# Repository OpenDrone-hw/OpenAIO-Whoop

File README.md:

# OpenAIO-Whoop

An all-in-one board for 1S: 65 and 75 mm tiny whoops, 1S toothpicks and 1S
long range on an 18650. Flight controller,
four brushless ESC channels, an ExpressLRS receiver and an onboard analog VTX
on the 25.5 x 25.5 mm whoop mounting pattern. The 1S sibling of
[OpenAIO](https://github.com/OpenDrone-hw/OpenAIO), which covers 3S to 6S on
the same mounting pattern.

## Why

Whoops are where an AIO is not a convenience but the only option: there is no room for a stack and no weight budget for connectors. 2S and up is OpenAIO's range, so what is left for a second board is 1S, where the power tree starts from a single cell and everything above battery voltage has to be boosted.

Analog is the reason this board is separate rather than a variant. A 1S whoop is the last class still flying analog in volume, and an onboard VTX is what makes the board worth building instead of pointing people at a digital AIO with an HD port.

## Specifications

| | |
|---|---|
| Target class | 1S whoops, 65 to 85 mm |
| Mounting | 25.5 x 25.5 mm, three D3.55 ear holes |
| Board | 26.4 mm body, 8-layer HDI 1+6+1, 0.997 mm |
| Input | 1S LiPo, solder pads J2 (+) and J3 (-) |
| MCU | RP2354A, 2 MB in-package flash |
| IMU | BMI270 on SPI |
| Blackbox | 16 MB SPI NOR flash (PY25Q128HA) |
| ESC | 4 channels, EFM8BB51 + 3 AGM210MAP half-bridges each, bidirectional DShot, Bluejay |
| Current sense | 0.5 mohm shunt + INA186A3, 50 mV/A |
| Receiver | Onboard ExpressLRS 2.4 GHz, ESP32-PICO-V3 + SX1281, wire antenna |
| Video | Onboard analog VTX, RTC6705 + SE5004L PA, U.FL |
| OSD | Analog, PIO framebuffer |
| Digital video | DJI O4 Lite pads: J26 VHD (+5V_BST), J28 TX0, J29 RX0, J27 GND (UART0); JST SH 1.0 mm 4-pin plug J35 (1 VHD, 2 GND, 3 TX, 4 RX) |
| Motors | Molex PicoBlade 1.25 mm 3-pin lands, plug or solder |
| USB | JST SH 1.0 mm 4-pin, J31 |
| Camera | JST SUR 0.8 mm 3-pin plug J32, solder pads J23 and J24 |
| Firmware | Betaflight (target in this repo), Bluejay, ExpressLRS |

Technical write-up, part list and layout constraints: [AGENTS.md](AGENTS.md). Pin map: [research/PINMAP.md](research/PINMAP.md). Firmware: [Betaflight target](firmware/betaflight/README.md), [ExpressLRS binding](firmware/expresslrs/README.md).

Open `hardware/OpenAIO-Whoop.kicad_pro` in KiCad 10 and keep the hardware folder together. The images above are renders of the routed board; this is not a manufacturing release.

## Constraints

- 25.5 x 25.5 mm mounting pattern, shared with OpenAIO.
- 1S only. 2S and above is OpenAIO.
- Motor plugs, USB, battery pads and camera plug follow the BetaFPV Matrix 1S 5IN1 II positions, so leads and cables reach as on that board.
- FC section follows the [OpenFC Lite 20x20](https://github.com/OpenDrone-hw/OpenFC-Lite-Mini) RP2354A design; receiver follows [OpenRX-Lite-UFL](https://github.com/OpenDrone-hw/OpenRX-Lite-UFL) (SX1281) on an ESP32-PICO-V3 that talks CRSF to the FC and also controls the VTX.
- Passives 0201 and up.
- No battery protection on the board: no reverse-polarity protection, no TVS, no low-cell cutoff.

### VTX control path

| Item | Value |
|---|---|
| Protocol | ExpressLRS MSP-VTX, CRSF receiver on UART1 (GPIO8/9) |
| VTX owner | ESP32-PICO-V3 drives the RTC6705 over SPI and the SE5004L reference through PA_EN (ESP32 GPIO21) |
| Pit mode | Does not drop PA_EN and does not stop SPI activity (see firmware/expresslrs/README.md) |
| HD hold-off | RP2354A GPIO19 (`HD_EN`) high permits analog VTX power, low switches it off; fixed HD builds set `pinio_config = 1,1,1,1` |

## Prior art

- [OpenFC Lite 20x20](https://github.com/OpenDrone-hw/OpenFC-Lite-Mini) and [OpenRX-Lite-UFL](https://github.com/OpenDrone-hw/OpenRX-Lite-UFL): the FC and RX stages this board follows.
- [OpenAIO](https://github.com/OpenDrone-hw/OpenAIO): the 3S to 6S board on the same mounting pattern.
- [OpenVTX](https://github.com/OpenDrone-hw/OpenVTX): the line's RTC6705 analog VTX.
- BetaFPV Matrix 1S 5IN1 II: the class reference.

## In the line

What pairs with what, and what is available:
[opendrone.be](https://opendrone.be).

## Contributing

See [CONTRIBUTING.md](CONTRIBUTING.md). KiCad files cannot be merged, so say what you intend to change before you do, on [Discord](https://discord.gg/v3sWmTcx3R).

Clone with the shared library:

```sh
git clone --recursive https://github.com/OpenDrone-hw/OpenAIO-Whoop
git submodule update --init      # after a plain git clone
```

Catalogue 3D models resolve through the project text variable `OPENDRONE_LIB` (`${KIPRJMOD}/KiCad-Library`), so without the submodule the 3D view shows bare pads.

A repository holds design files only. Sourcing (suppliers, prices, quotes, RFQs, contacts) is handled by Incutec and never lives in OpenDrone repositories.

## License

Hardware licensed under [CERN-OHL-S-2.0](https://ohwr.org/cern_ohl_s_v2.txt),
see [LICENSE](LICENSE).

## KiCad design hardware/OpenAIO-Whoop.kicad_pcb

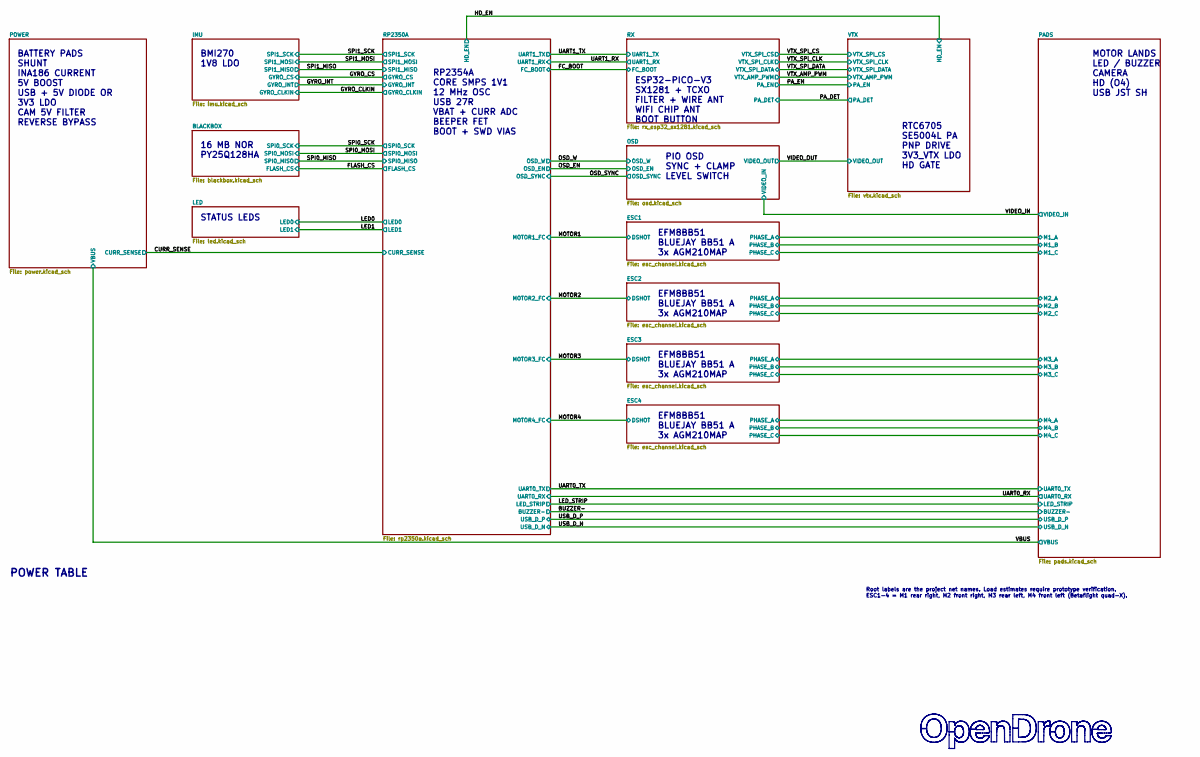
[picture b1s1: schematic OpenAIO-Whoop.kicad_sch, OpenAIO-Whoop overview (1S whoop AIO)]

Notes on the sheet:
PIO OSD SYNC + CLAMP LEVEL SWITCH
EFM8BB51 BLUEJAY BB51 A 3x AGM210MAP
16 MB NOR PY25Q128HA
POWER TABLE
STATUS LEDS
ESP32-PICO-V3 SX1281 + TCXO FILTER + WIRE ANT WIFI CHIP ANT BOOT BUTTON
BATTERY PADS SHUNT INA186 CURRENT 5V BOOST USB + 5V DIODE OR 3V3 LDO CAM 5V FILTER REVERSE BYPASS
MOTOR LANDS LED / BUZZER CAMERA HD (O4) USB JST SH
RTC6705 SE5004L PA PNP DRIVE 3V3_VTX LDO HD GATE
RP2354A CORE SMPS 1V1 12 MHz OSC USB 27R VBAT + CURR ADC BEEPER FET BOOT + SWD VIAS
BMI270 1V8 LDO
Root labels are the project net names. Load estimates require prototype verification. ESC1-4 = M1 rear right, M2 front right, M3 rear left, M4 front left (Betaflight quad-X).

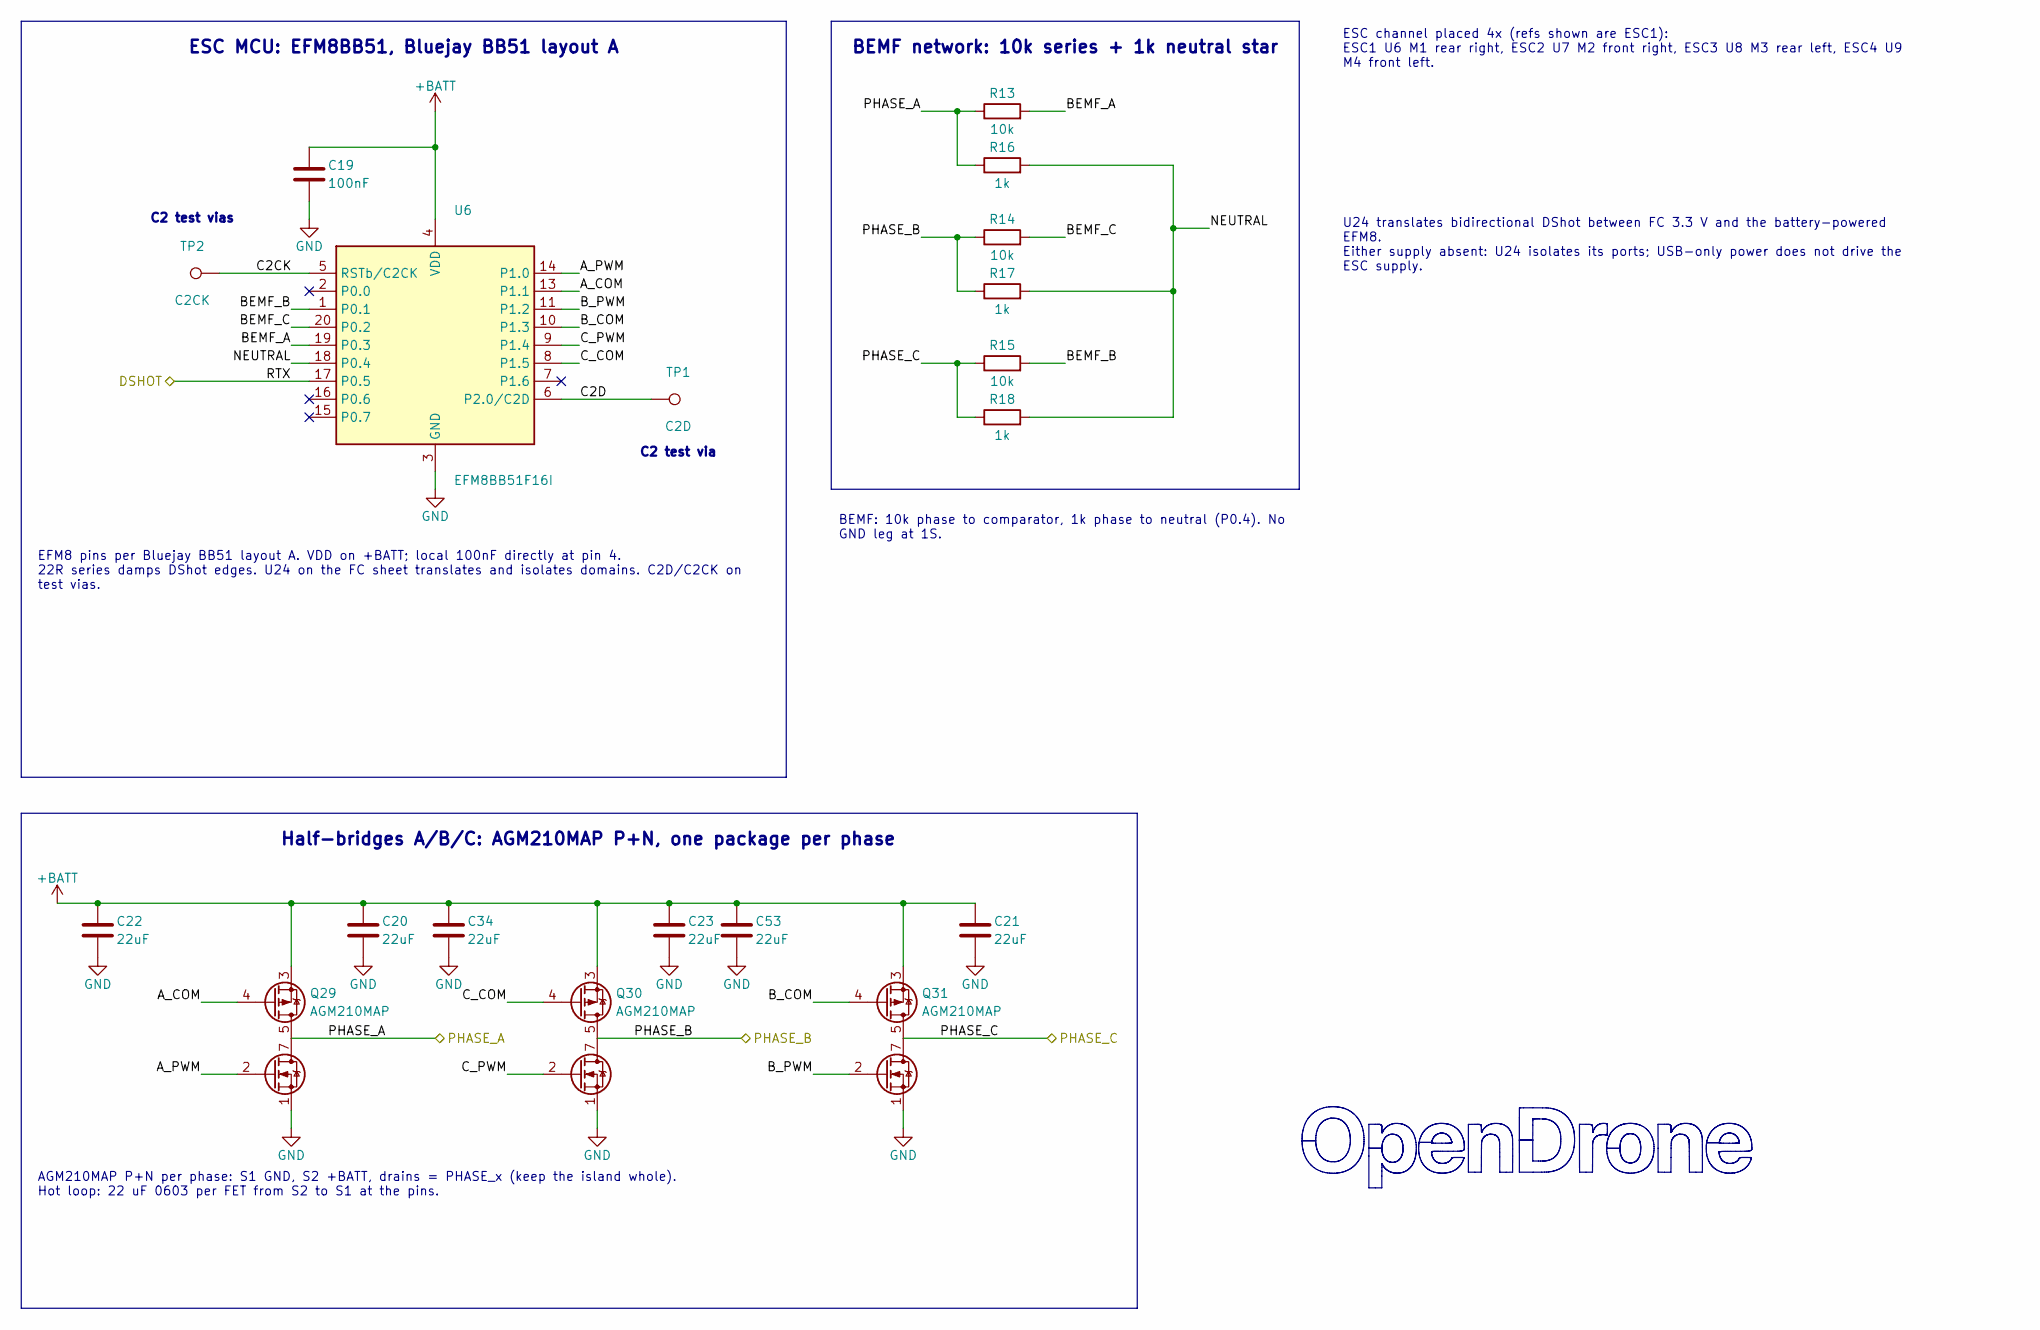
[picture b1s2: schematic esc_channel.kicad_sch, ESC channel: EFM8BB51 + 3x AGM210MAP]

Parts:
C19: 100nF; C_0201_0603Metric_L; MPN GRM033C81E104KE14D; LCSC C181047
C20, C21, C22, C23, C34, C53: 22uF; C_0603_1608Metric_L; MPN GRM188C80J226ME15D; LCSC C393031
Q29, Q30, Q31: AGM210MAP; AGM_PDFN-8-2EP_3.3x3.3mm_AGM210MAP_L; MPN AGM210MAP; LCSC C7431169
R13, R14, R15: 10k; R_0201_0603Metric_L; MPN RC0201FR-0710KL; LCSC C106225
R16, R17, R18: 1k; R_0201_0603Metric_L; MPN RC0201FR-071KL; LCSC C138165
TP1: C2D; TestPoint_Pad_D0.8mm
TP2: C2CK; TestPoint_Pad_D0.8mm
U6: EFM8BB51F16I; QFN-20_3x3mm_P0.5mm_EFM8BB51_L; MPN EFM8BB51F16I-C-QFN20R; LCSC C3232998

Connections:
+BATT: C19.1, C20.1, C21.1, C22.1, C23.1, C34.1, Q29.3 (S2), Q30.3 (S2), Q31.3 (S2), U6.4 (VDD); also elsewhere on the board
/ESC1/A_COM: Q29.4 (G2), U6.13 (P1.1)
/ESC1/A_PWM: Q29.2 (G1), U6.14 (P1.0)
/ESC1/BEMF_A: R13.2, U6.19 (P0.3)
/ESC1/BEMF_B: R15.2, U6.1 (P0.1)
/ESC1/BEMF_C: R14.2, U6.20 (P0.2)
/ESC1/B_COM: Q31.4 (G2), U6.10 (P1.3)
/ESC1/B_PWM: Q31.2 (G1), U6.11 (P1.2)
/ESC1/C2CK: TP2.1 (1_1), U6.5 (RSTb/C2CK)
/ESC1/C2D: TP1.1 (1_1), U6.6 (P2.0/C2D)
/ESC1/C_COM: Q30.4 (G2), U6.8 (P1.5)
/ESC1/C_PWM: Q30.2 (G1), U6.9 (P1.4)
/ESC1/NEUTRAL: R16.2, R17.2, R18.2, U6.18 (P0.4)
/ESC1/PHASE_A: Q29.5 (D2), Q29.6 (D2), Q29.7 (D1), Q29.8 (D1), R13.1, R16.1; also elsewhere on the board
/ESC1/PHASE_B: Q30.5 (D2), Q30.6 (D2), Q30.7 (D1), Q30.8 (D1), R14.1, R17.1; also elsewhere on the board
/ESC1/PHASE_C: Q31.5 (D2), Q31.6 (D2), Q31.7 (D1), Q31.8 (D1), R15.1, R18.1; also elsewhere on the board
/MOTOR1: U6.17 (P0.5); also elsewhere on the board
GND: C19.2, C20.2, C21.2, C22.2, C23.2, C34.2, Q29.1 (S1), Q30.1 (S1), Q31.1 (S1), U6.3 (GND), U6.12 (GND), U6.21 (GND); also elsewhere on the board

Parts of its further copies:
C24, C26, C27, C28, C29, C30, C32, C33, C35, C36, C38, C39, C40, C41, C43, C63: 22uF; C_0603_1608Metric_L; MPN GRM188C80J226ME15D; LCSC C393031
Q32, Q33, Q34, Q35, Q36, Q37, Q38, Q39, Q40: AGM210MAP; AGM_PDFN-8-2EP_3.3x3.3mm_AGM210MAP_L; MPN AGM210MAP; LCSC C7431169
R20, R21, R22, R27, R28, R29, R34, R35, R36: 10k; R_0201_0603Metric_L; MPN RC0201FR-0710KL; LCSC C106225
R23, R24, R25, R30, R31, R32, R37, R38, R39: 1k; R_0201_0603Metric_L; MPN RC0201FR-071KL; LCSC C138165
TP3, TP5, TP7: C2D; TestPoint_Pad_D0.8mm
TP4, TP6, TP8: C2CK; TestPoint_Pad_D0.8mm
U7, U8, U9: EFM8BB51F16I; QFN-20_3x3mm_P0.5mm_EFM8BB51_L; MPN EFM8BB51F16I-C-QFN20R; LCSC C3232998

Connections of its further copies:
+BATT: C24.1, C26.1, C27.1, C28.1, C29.1, C30.1, C32.1, C33.1, C35.1, C36.1, C38.1, C39.1, C40.1, C41.1, C43.1, C63.1, Q32.3 (S2), Q33.3 (S2), Q34.3 (S2), Q35.3 (S2), Q36.3 (S2), Q37.3 (S2), Q38.3 (S2), Q39.3 (S2), Q40.3 (S2), U7.4 (VDD), U8.4 (VDD), U9.4 (VDD); also elsewhere on the board
/ESC2/A_COM: Q32.4 (G2), U7.13 (P1.1)
/ESC2/A_PWM: Q32.2 (G1), U7.14 (P1.0)
/ESC2/BEMF_A: R20.2, U7.19 (P0.3)
/ESC2/BEMF_B: R22.2, U7.1 (P0.1)
/ESC2/BEMF_C: R21.2, U7.20 (P0.2)
/ESC2/B_COM: Q34.4 (G2), U7.10 (P1.3)
/ESC2/B_PWM: Q34.2 (G1), U7.11 (P1.2)
/ESC2/C2CK: TP4.1 (1_1), U7.5 (RSTb/C2CK)
/ESC2/C2D: TP3.1 (1_1), U7.6 (P2.0/C2D)
/ESC2/C_COM: Q33.4 (G2), U7.8 (P1.5)
/ESC2/C_PWM: Q33.2 (G1), U7.9 (P1.4)
/ESC2/NEUTRAL: R23.2, R24.2, R25.2, U7.18 (P0.4)
/ESC2/PHASE_A: Q32.5 (D2), Q32.6 (D2), Q32.7 (D1), Q32.8 (D1), R20.1, R23.1; also elsewhere on the board
/ESC2/PHASE_B: Q33.5 (D2), Q33.6 (D2), Q33.7 (D1), Q33.8 (D1), R21.1, R24.1; also elsewhere on the board
/ESC2/PHASE_C: Q34.5 (D2), Q34.6 (D2), Q34.7 (D1), Q34.8 (D1), R22.1, R25.1; also elsewhere on the board
/ESC3/A_COM: Q35.4 (G2), U8.13 (P1.1)
/ESC3/A_PWM: Q35.2 (G1), U8.14 (P1.0)
/ESC3/BEMF_A: R27.2, U8.19 (P0.3)
/ESC3/BEMF_B: R29.2, U8.1 (P0.1)
/ESC3/BEMF_C: R28.2, U8.20 (P0.2)
/ESC3/B_COM: Q37.4 (G2), U8.10 (P1.3)
/ESC3/B_PWM: Q37.2 (G1), U8.11 (P1.2)
/ESC3/C2CK: TP6.1 (1_1), U8.5 (RSTb/C2CK)
/ESC3/C2D: TP5.1 (1_1), U8.6 (P2.0/C2D)
/ESC3/C_COM: Q36.4 (G2), U8.8 (P1.5)
/ESC3/C_PWM: Q36.2 (G1), U8.9 (P1.4)
/ESC3/NEUTRAL: R30.2, R31.2, R32.2, U8.18 (P0.4)
/ESC3/PHASE_A: Q35.5 (D2), Q35.6 (D2), Q35.7 (D1), Q35.8 (D1), R27.1, R30.1; also elsewhere on the board
/ESC3/PHASE_B: Q36.5 (D2), Q36.6 (D2), Q36.7 (D1), Q36.8 (D1), R28.1, R31.1; also elsewhere on the board
/ESC3/PHASE_C: Q37.5 (D2), Q37.6 (D2), Q37.7 (D1), Q37.8 (D1), R29.1, R32.1; also elsewhere on the board
/ESC4/A_COM: Q38.4 (G2), U9.13 (P1.1)
/ESC4/A_PWM: Q38.2 (G1), U9.14 (P1.0)
/ESC4/BEMF_A: R34.2, U9.19 (P0.3)
/ESC4/BEMF_B: R36.2, U9.1 (P0.1)
/ESC4/BEMF_C: R35.2, U9.20 (P0.2)
/ESC4/B_COM: Q40.4 (G2), U9.10 (P1.3)
/ESC4/B_PWM: Q40.2 (G1), U9.11 (P1.2)
/ESC4/C2CK: TP8.1 (1_1), U9.5 (RSTb/C2CK)
/ESC4/C2D: TP7.1 (1_1), U9.6 (P2.0/C2D)
/ESC4/C_COM: Q39.4 (G2), U9.8 (P1.5)
/ESC4/C_PWM: Q39.2 (G1), U9.9 (P1.4)
/ESC4/NEUTRAL: R37.2, R38.2, R39.2, U9.18 (P0.4)
/ESC4/PHASE_A: Q38.5 (D2), Q38.6 (D2), Q38.7 (D1), Q38.8 (D1), R34.1, R37.1; also elsewhere on the board
/ESC4/PHASE_B: Q39.5 (D2), Q39.6 (D2), Q39.7 (D1), Q39.8 (D1), R35.1, R38.1; also elsewhere on the board
/ESC4/PHASE_C: Q40.5 (D2), Q40.6 (D2), Q40.7 (D1), Q40.8 (D1), R36.1, R39.1; also elsewhere on the board
/MOTOR2: U7.17 (P0.5); also elsewhere on the board
/MOTOR3: U8.17 (P0.5); also elsewhere on the board
/MOTOR4: U9.17 (P0.5); also elsewhere on the board
GND: C24.2, C26.2, C27.2, C28.2, C29.2, C30.2, C32.2, C33.2, C35.2, C36.2, C38.2, C39.2, C40.2, C41.2, C43.2, C63.2, Q32.1 (S1), Q33.1 (S1), Q34.1 (S1), Q35.1 (S1), Q36.1 (S1), Q37.1 (S1), Q38.1 (S1), Q39.1 (S1), Q40.1 (S1), U7.3 (GND), U7.12 (GND), U7.21 (GND), U8.3 (GND), U8.12 (GND), U8.21 (GND), U9.3 (GND), U9.12 (GND), U9.21 (GND); also elsewhere on the board

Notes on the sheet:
C2 test vias
Half-bridges A/B/C: AGM210MAP P+N, one package per phase
ESC MCU: EFM8BB51, Bluejay BB51 layout A
BEMF network: 10k series + 1k neutral star
C2 test via
AGM210MAP P+N per phase: S1 GND, S2 +BATT, drains = PHASE_x (keep the island whole). Hot loop: 22 uF 0603 per FET from S2 to S1 at the pins.
ESC channel placed 4x (refs shown are ESC1): ESC1 U6 M1 rear right, ESC2 U7 M2 front right, ESC3 U8 M3 rear left, ESC4 U9 M4 front left.
U24 translates bidirectional DShot between FC 3.3 V and the battery-powered EFM8. Either supply absent: U24 isolates its ports; USB-only power does not drive the ESC supply.
EFM8 pins per Bluejay BB51 layout A. VDD on +BATT; local 100nF directly at pin 4. 22R series damps DShot edges. U24 on the FC sheet translates and isolates domains. C2D/C2CK on test vias.
BEMF: 10k phase to comparator, 1k phase to neutral (P0.4). No GND leg at 1S.

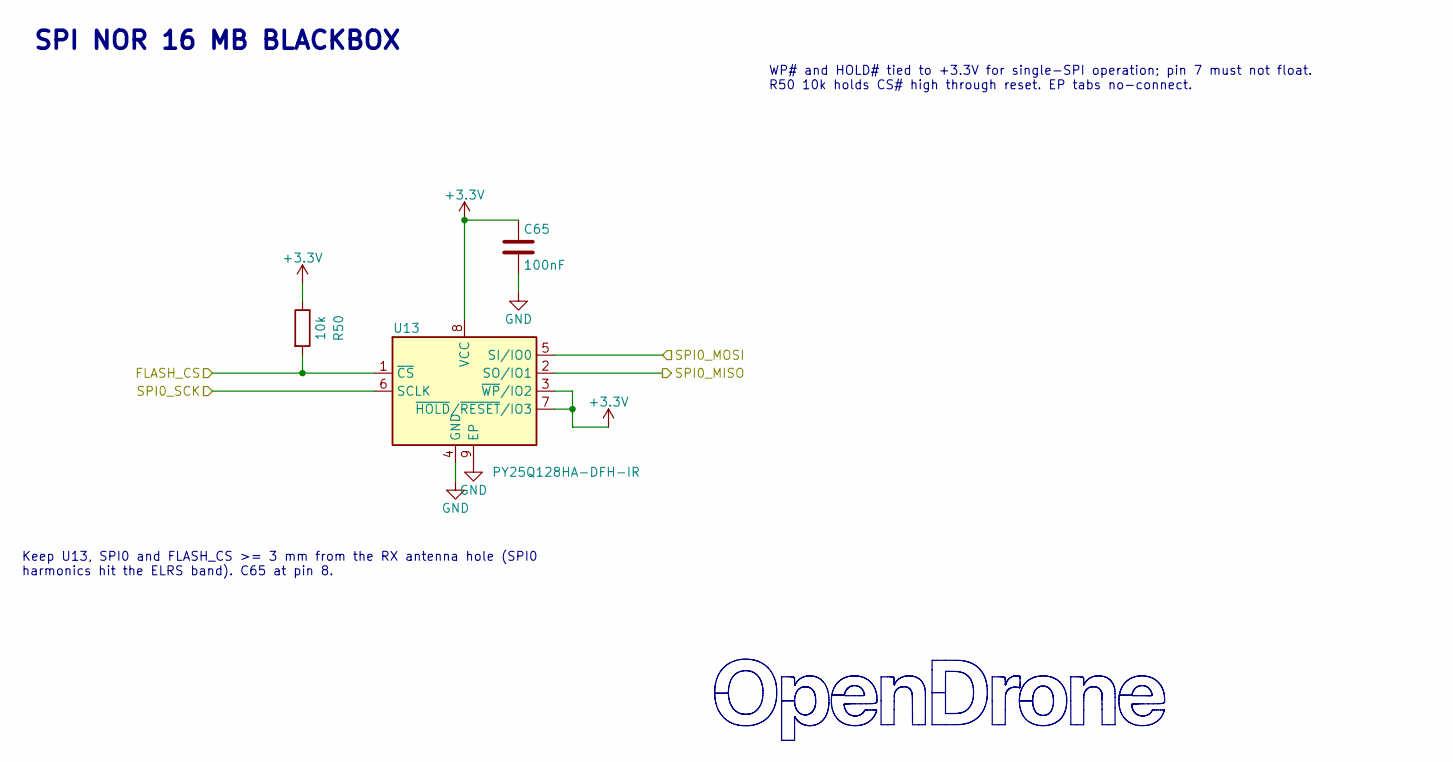
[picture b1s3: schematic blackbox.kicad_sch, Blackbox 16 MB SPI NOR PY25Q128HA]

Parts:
C65: 100nF; C_0201_0603Metric_L; MPN GRM033C81E104KE14D; LCSC C181047
R50: 10k; R_0201_0603Metric_L; MPN RC0201FR-0710KL; LCSC C106225
U13: PY25Q128HA-DFH-IR; USON-8_3x3mm_P0.8mm_EP_PY25Q128HA_L; MPN PY25Q128HA-DFH-IR; LCSC C53467986

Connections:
+3.3V: C65.1, R50.1, U13.3 (~WP/IO2), U13.7 (~HOLD/~RESET/IO3), U13.8 (VCC); also elsewhere on the board
/FLASH_CS: R50.2, U13.1 (~CS); also elsewhere on the board
/SPI0_MISO: U13.2 (SO/IO1); also elsewhere on the board
/SPI0_MOSI: U13.5 (SI/IO0); also elsewhere on the board
/SPI0_SCK: U13.6 (SCLK); also elsewhere on the board
GND: C65.2, U13.4 (GND), U13.9 (EP); also elsewhere on the board

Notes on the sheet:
SPI NOR 16 MB BLACKBOX
Keep U13, SPI0 and FLASH_CS >= 3 mm from the RX antenna hole (SPI0 harmonics hit the ELRS band). C65 at pin 8.
WP# and HOLD# tied to +3.3V for single-SPI operation; pin 7 must not float. R50 10k holds CS# high through reset. EP tabs no-connect.

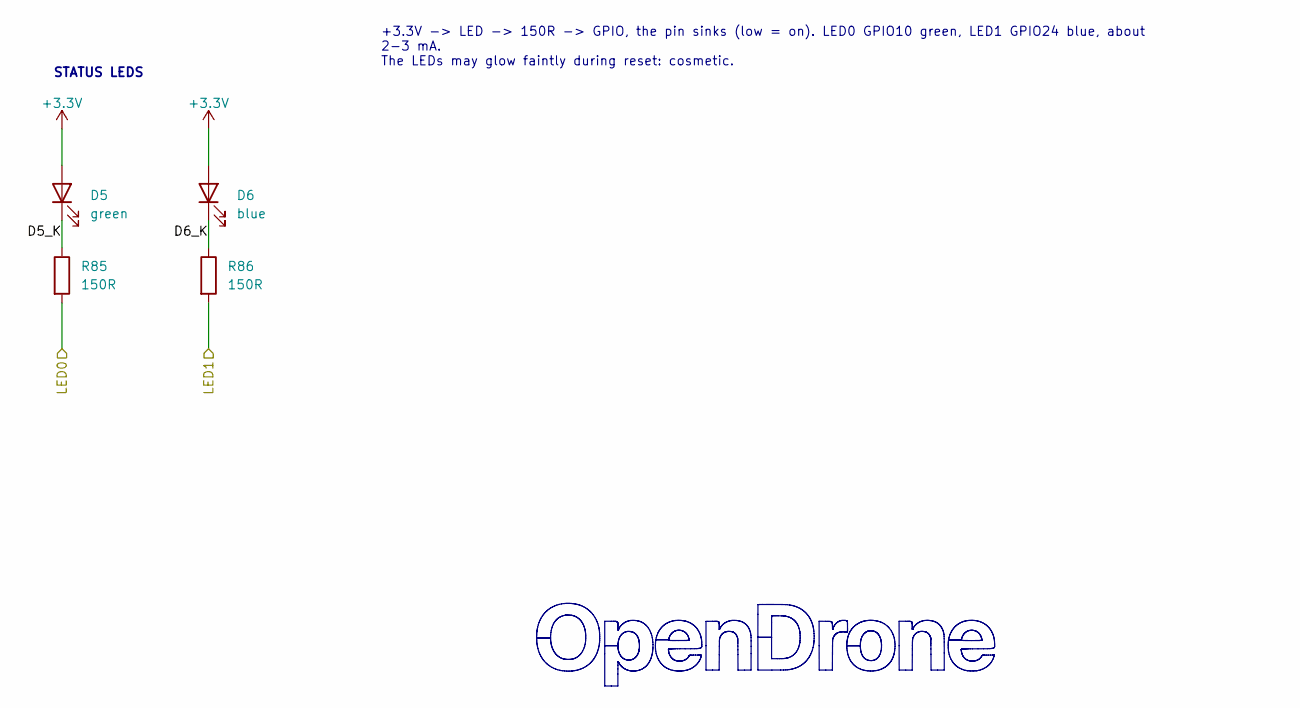
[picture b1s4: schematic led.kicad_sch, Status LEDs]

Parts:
D5: green; LED_0402_1005Metric_L; MPN XL-1005UGC; LCSC C965793
D6: blue; LED_0402_1005Metric_L; MPN XL-1005UBC; LCSC C22355736
R85, R86: 150R; R_0201_0603Metric_L; MPN RC0201FR-07150RL; LCSC C295773

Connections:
+3.3V: D5.2 (A), D6.2 (A); also elsewhere on the board
/LED0: R85.2; also elsewhere on the board
/LED1: R86.2; also elsewhere on the board
/LED/D5_K: D5.1 (K), R85.1
/LED/D6_K: D6.1 (K), R86.1

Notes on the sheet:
STATUS LEDS
+3.3V -> LED -> 150R -> GPIO, the pin sinks (low = on). LED0 GPIO10 green, LED1 GPIO24 blue, about 2-3 mA. The LEDs may glow faintly during reset: cosmetic.

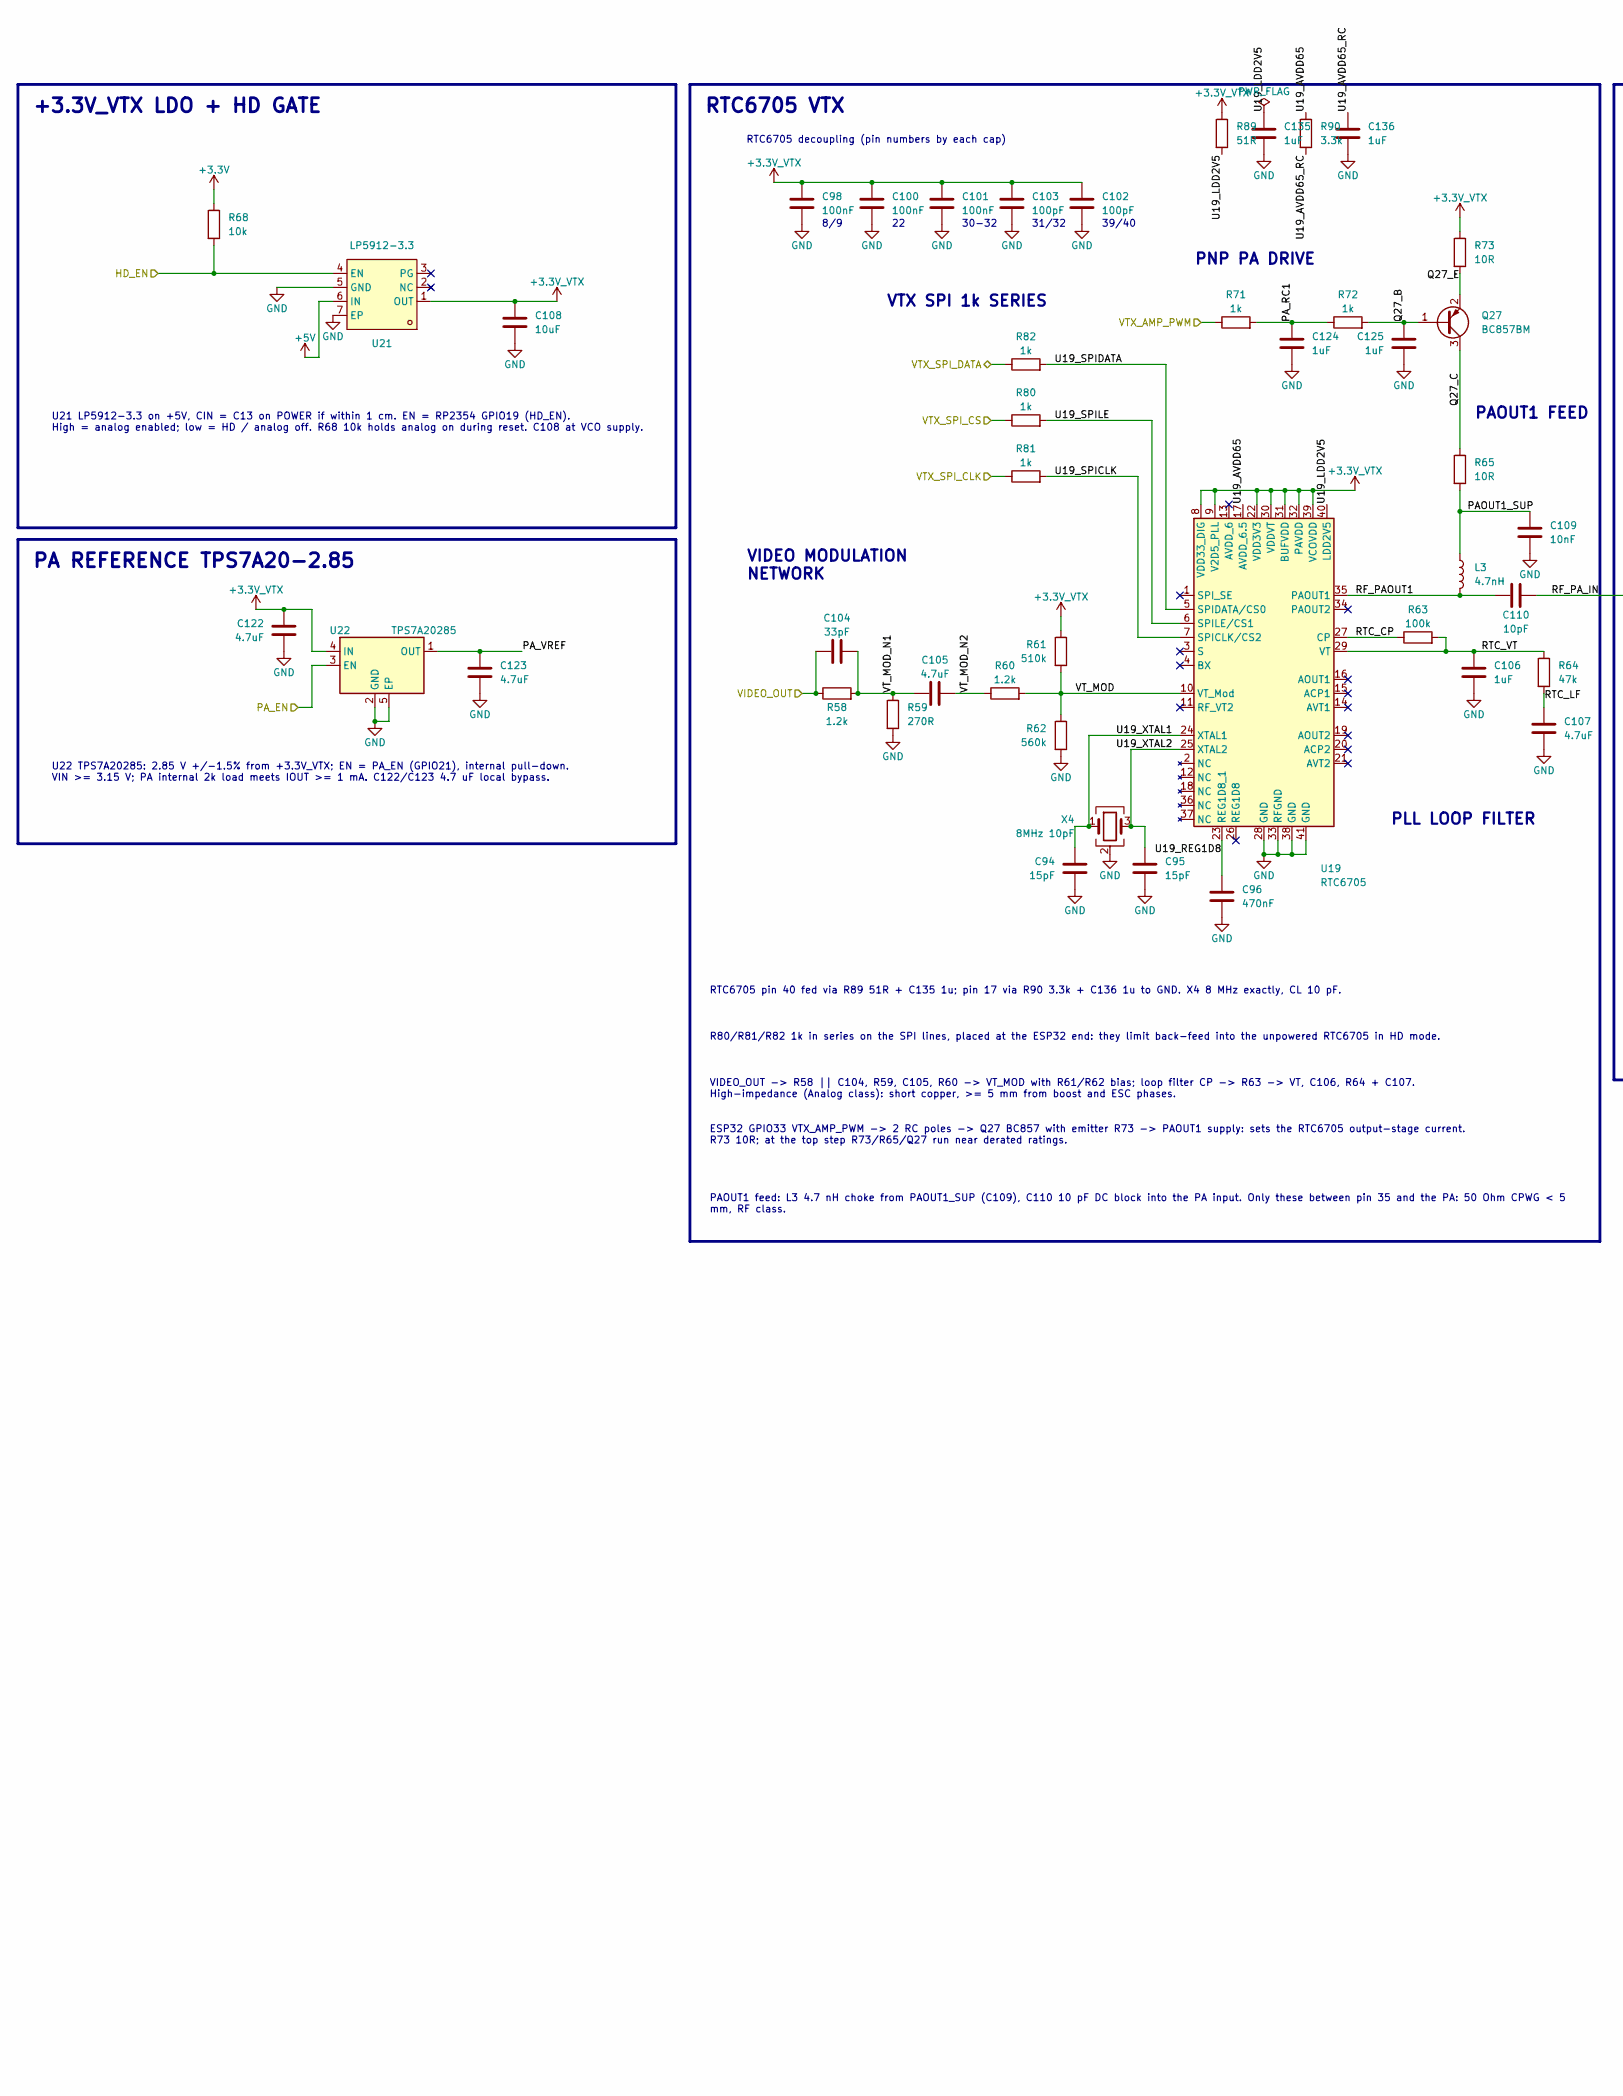
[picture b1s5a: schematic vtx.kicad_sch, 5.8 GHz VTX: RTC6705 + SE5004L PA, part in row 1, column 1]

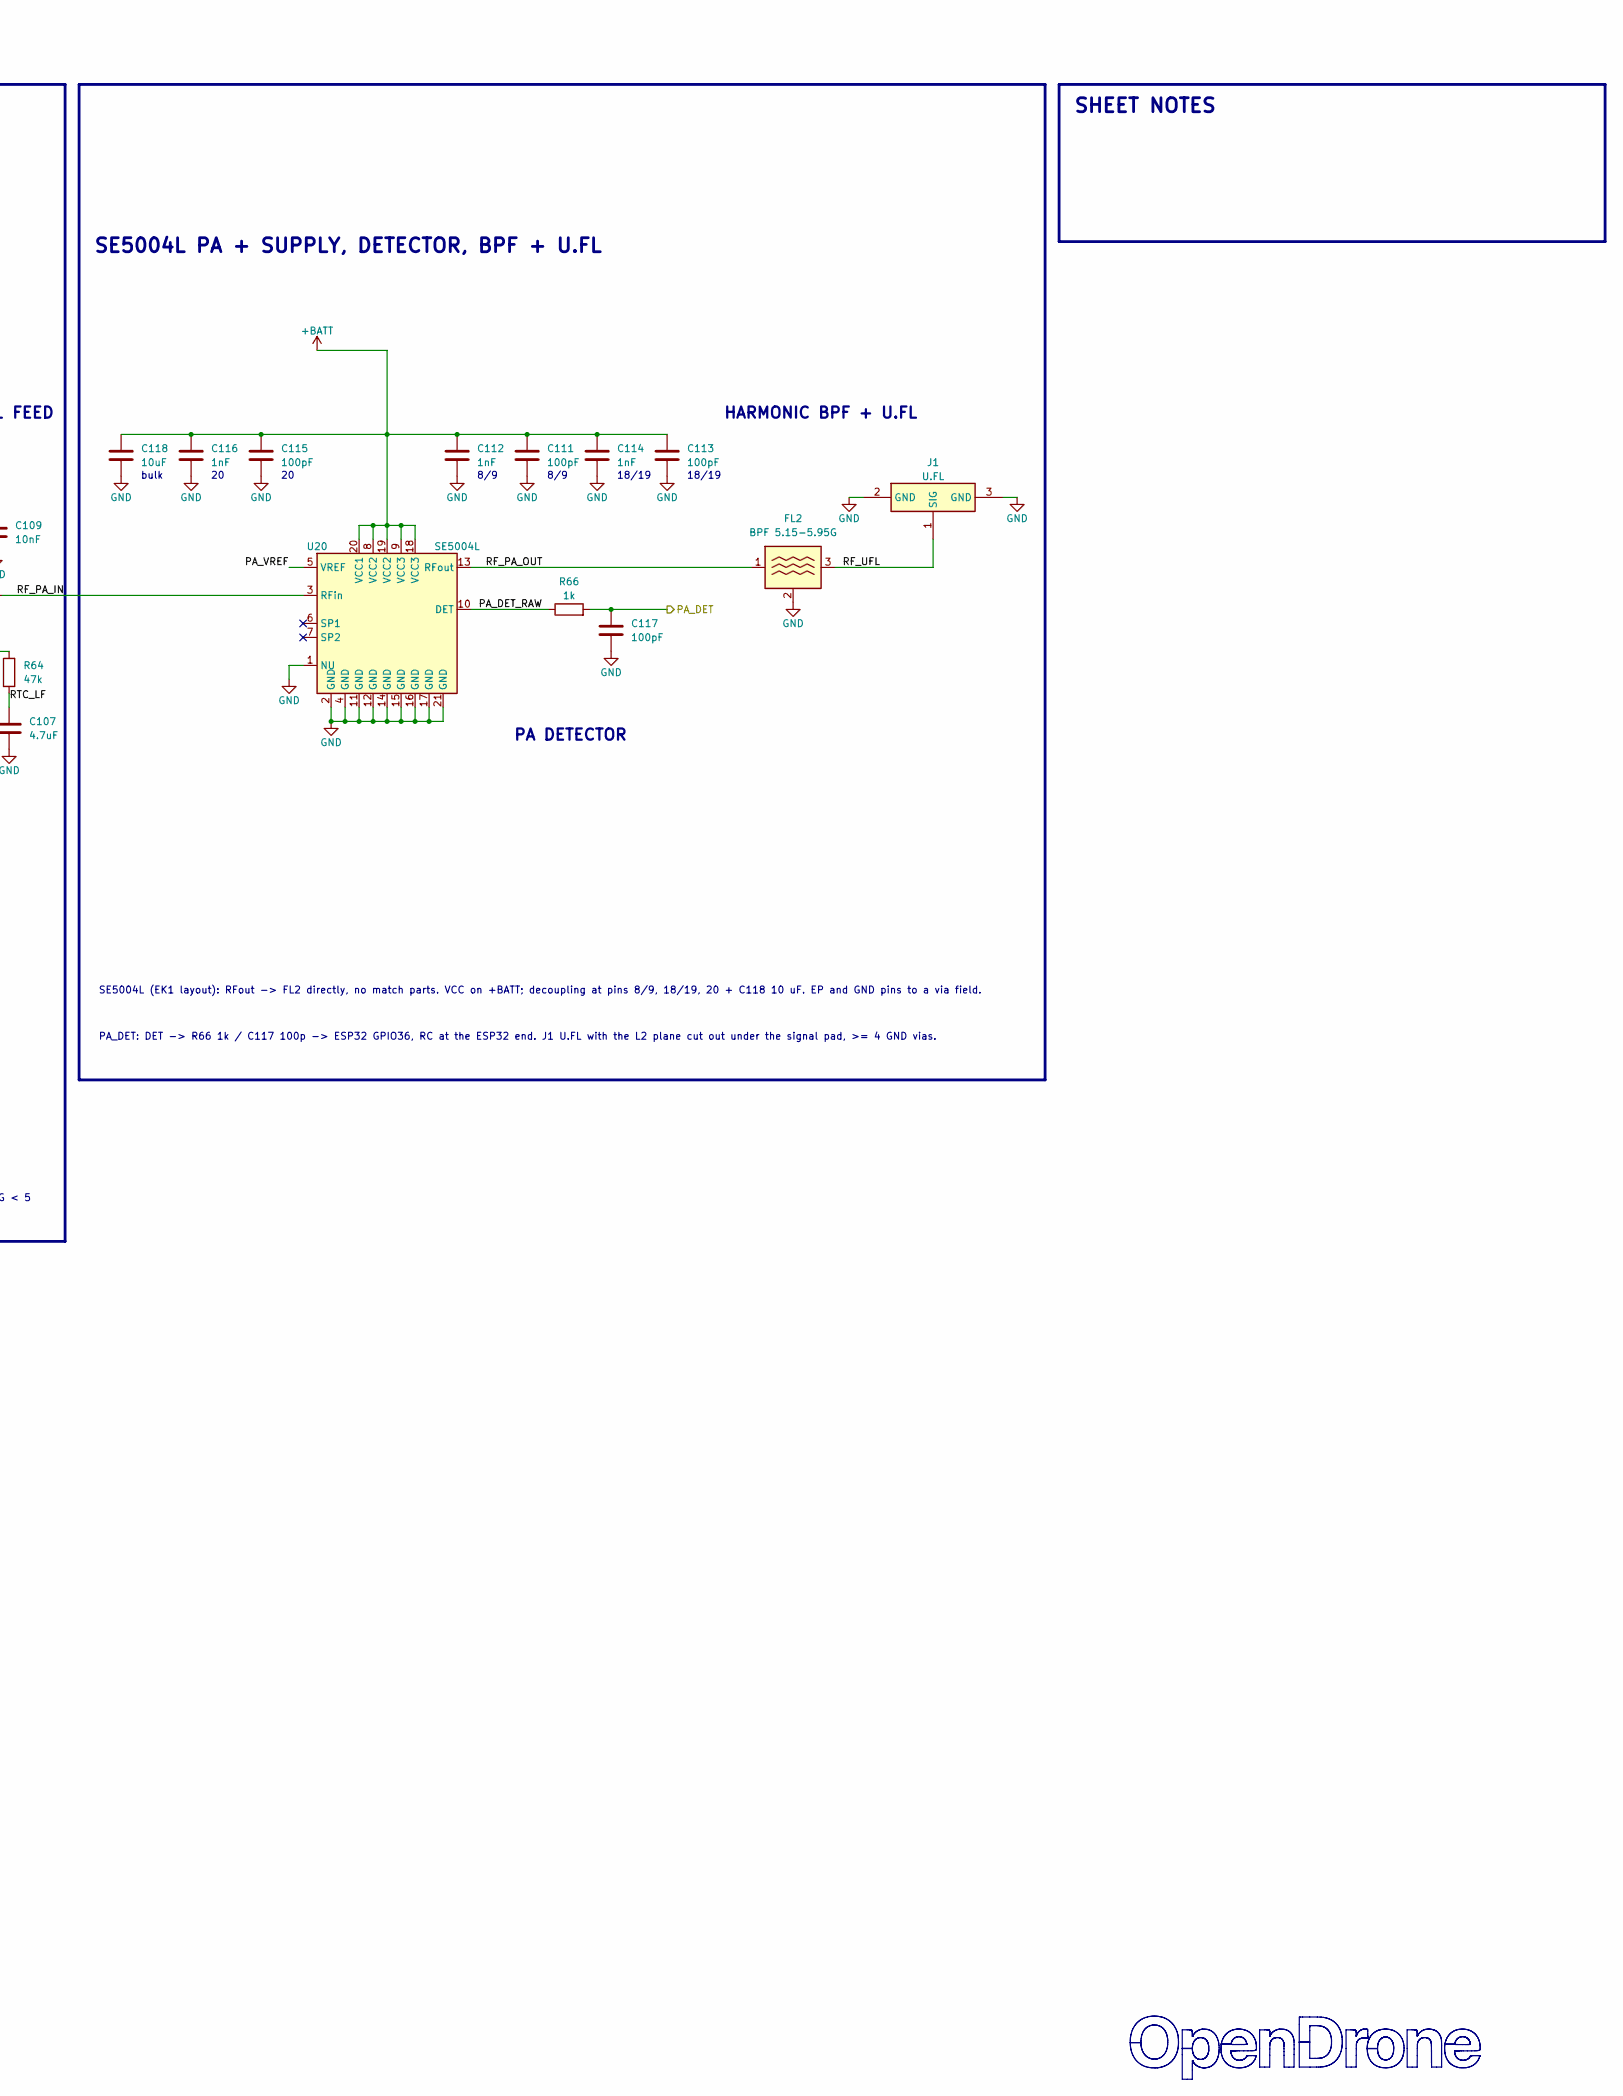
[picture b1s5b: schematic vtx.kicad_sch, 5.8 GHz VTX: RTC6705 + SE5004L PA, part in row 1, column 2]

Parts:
C94, C95: 15pF; C_0201_0603Metric_L; MPN GRM0335C1H150JA01D; LCSC C85891
C96: 470nF; C_0201_0603Metric_L; MPN GRM033R60J474KE90D; LCSC C85926
C98, C100, C101: 100nF; C_0201_0603Metric_L; MPN GRM033C81E104KE14D; LCSC C181047
C102, C103, C111, C113, C115, C117: 100pF; C_0201_0603Metric_L; MPN GRM0335C1H101JA01D; LCSC C76922
C104: 33pF; C_0201_0603Metric_L; MPN GRM0335C1H330JA01D; LCSC C76925
C105, C107: 4.7uF; C_0402_1005Metric_L; MPN CL05A475MP5NRNC; LCSC C23733
C106: 1uF; C_0402_1005Metric_L; MPN CL05A105KA5NQNC; LCSC C52923
C108, C118: 10uF; C_0402_1005Metric_L; MPN GRM155C80J106ME11D; LCSC C237279
C109: 10nF; C_0201_0603Metric_L; MPN GRM033R71A103KA01D; LCSC C76941
C110: 10pF; C_0201_0603Metric_L; MPN GRM0335C1H100JA01D; LCSC C76921
C112, C114, C116: 1nF; C_0201_0603Metric_L; MPN GRM033R71H102KA12D; LCSC C85934
C122, C123: 4.7uF; C_0201_0603Metric_L; MPN GRM035R60J475ME15D; LCSC C335103
C124, C125, C135, C136: 1uF; C_0201_0603Metric_L; MPN GRM033R61A105ME44D; LCSC C76935
FL2: BPF 5.15-5.95G; Walsin_RFBPF1608060K98Q1C; MPN RFBPF1608060K98Q1C; LCSC C2442150
J1: U.FL; U.FL_Hirose_U.FL-R-SMT-1_Vertical_L; MPN U.FL-R-SMT-1(80); LCSC C88374
L3: 4.7nH; L_0201_0603Metric_L; MPN LQP03TN4N7H02D; LCSC C86126
Q27: BC857BM; DFN-3L_L1.0-W0.6-P0.65-BR_W; MPN BC857BM,315; LCSC C549525
R58, R60: 1.2k; R_0201_0603Metric_L; MPN RC0201FR-071K2L; LCSC C327393
R59: 270R; R_0201_0603Metric_L; MPN RC0201FR-07270RL; LCSC C295793
R61: 510k; R_0201_0603Metric_L; MPN RC0201FR-07510KL; LCSC C295805
R62: 560k; R_0201_0603Metric_L; MPN RC0201FR-07560KL; LCSC C295807
R63: 100k; R_0201_0603Metric_L; MPN RC0201FR-07100KL; LCSC C106224
R64: 47k; R_0201_0603Metric_L; MPN RC0201FR-0747KL; LCSC C138139
R65, R73: 10R; R_0201_0603Metric_L; MPN RC0201FR-0710RL; LCSC C106226
R66, R71, R72, R80, R81, R82: 1k; R_0201_0603Metric_L; MPN RC0201FR-071KL; LCSC C138165
R68: 10k; R_0201_0603Metric_L; MPN RC0201FR-0710KL; LCSC C106225
R89: 51R; R_0201_0603Metric_L; MPN RC0201FR-0751RL; LCSC C163499
R90: 3.3k; R_0201_0603Metric_L; MPN RC0201FR-073K3L; LCSC C274874
U19: RTC6705; QFN-40_6x6mm_P0.5mm_EP_RTC6705_L; MPN RTC6705; LCSC C913074
U20: SE5004L; QFN-20_4x4mm_P0.5mm_EP_SE5004L_L; MPN SE5004L-R; LCSC C210263
U21: LP5912-3.3; WSON-6-1EP_2x2mm_P0.65mm_EP1x1.6mm_L; MPN LP5912-3.3DRVR; LCSC C524780
U22: TPS7A20285; X2SON-4_L1.0-W1.0-P0.65-TL-EP_Dense; MPN TPS7A20285PDQNR; LCSC C3748388
X4: 8MHz 10pF; CRYSTAL-SMD_4P-L3.2-W2.5-BL_Dense; MPN TAXM8M4RDBCCT2T; LCSC C400090

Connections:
+3.3V: R68.1; also elsewhere on the board
+3.3V_VTX: C98.1, C100.1, C101.1, C102.1, C103.1, C108.1, C122.1, R61.1, R73.1, R89.1, U19.8 (VDD33_DIG), U19.9 (V2D5_PLL), U19.22 (VDD3V3), U19.30 (VDDVT), U19.31 (BUFVDD), U19.32 (PAVDD), U19.39 (VCOVDD), U21.1 (OUT), U22.4 (IN)
+5V: U21.6 (IN); also elsewhere on the board
+BATT: C111.1, C112.1, C113.1, C114.1, C115.1, C116.1, C118.1, U20.8 (VCC2), U20.9 (VCC3), U20.18 (VCC3), U20.19 (VCC2), U20.20 (VCC1); also elsewhere on the board
/HD_EN: R68.2, U21.4 (EN); also elsewhere on the board
/PA_DET: C117.1, R66.2; also elsewhere on the board
/PA_EN: U22.3 (EN); also elsewhere on the board
/VIDEO_OUT: C104.1, R58.1; also elsewhere on the board
/VTX/PAOUT1_SUP: C109.1, L3.1, R65.2
/VTX/PA_DET_RAW: R66.1, U20.10 (DET)
/VTX/PA_RC1: C124.1, R71.2, R72.1
/VTX/PA_VREF: C123.1, U20.5 (VREF), U22.1 (OUT)
/VTX/Q27_B: C125.1, Q27.1 (B), R72.2
/VTX/Q27_C: Q27.3 (C), R65.1
/VTX/Q27_E: Q27.2 (E), R73.2
/VTX/RF_PAOUT1: C110.1, L3.2, U19.35 (PAOUT1)
/VTX/RF_PA_IN: C110.2, U20.3 (RFin)
/VTX/RF_PA_OUT: FL2.1 (IN), U20.13 (RFout)
/VTX/RF_UFL: FL2.3 (OUT), J1.1 (SIG)
/VTX/RTC_CP: R63.1, U19.27 (CP)
/VTX/RTC_LF: C107.1, R64.2
/VTX/RTC_VT: C106.1, R63.2, R64.1, U19.29 (VT)
/VTX/U19_AVDD65: R90.1, U19.17 (AVDD_6.5)
/VTX/U19_AVDD65_RC: C136.1, R90.2
/VTX/U19_LDD2V5: C135.1, R89.2, U19.40 (LDD2V5)
/VTX/U19_REG1D8: C96.1, U19.23 (REG1D8_1)
/VTX/U19_SPICLK: R81.2, U19.7 (SPICLK/CS2)
/VTX/U19_SPIDATA: R82.2, U19.5 (SPIDATA/CS0)
/VTX/U19_SPILE: R80.2, U19.6 (SPILE/CS1)
/VTX/U19_XTAL1: C94.1, U19.24 (XTAL1), X4.1
/VTX/U19_XTAL2: C95.1, U19.25 (XTAL2), X4.3
/VTX/VT_MOD: R60.2, R61.2, R62.1, U19.10 (VT_Mod)
/VTX/VT_MOD_N1: C104.2, C105.1, R58.2, R59.1
/VTX/VT_MOD_N2: C105.2, R60.1
/VTX_AMP_PWM: R71.1; also elsewhere on the board
/VTX_SPI_CLK: R81.1; also elsewhere on the board
/VTX_SPI_CS: R80.1; also elsewhere on the board
/VTX_SPI_DATA: R82.1; also elsewhere on the board
GND: C94.2, C95.2, C96.2, C98.2, C100.2, C101.2, C102.2, C103.2, C106.2, C107.2, C108.2, C109.2, C111.2, C112.2, C113.2, C114.2, C115.2, C116.2, C117.2, C118.2, C122.2, C123.2, C124.2, C125.2, C135.2, C136.2, FL2.2 (GND), J1.2 (GND), J1.3 (GND), R59.2, R62.2, U19.28 (GND), U19.33 (RFGND), U19.38 (GND), U19.41 (GND), U20.1 (NU), U20.2 (GND), U20.4 (GND), U20.11 (GND), U20.12 (GND), U20.14 (GND), U20.15 (GND), U20.16 (GND), U20.17 (GND), U20.21 (GND), U21.5 (GND), U21.7 (EP), U22.2 (GND), U22.5 (EP), X4.2 (G), X4.4 (G); also elsewhere on the board

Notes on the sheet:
VIDEO MODULATION NETWORK
18/19
39/40
8/9
RTC6705 VTX
SE5004L PA + SUPPLY, DETECTOR, BPF + U.FL
+3.3V_VTX LDO + HD GATE
HARMONIC BPF + U.FL
bulk
PA DETECTOR
SHEET NOTES
PLL LOOP FILTER
RTC6705 decoupling (pin numbers by each cap)
PNP PA DRIVE
VTX SPI 1k SERIES
PAOUT1 FEED
31/32
PA REFERENCE TPS7A20-2.85
30-32
U22 TPS7A20285: 2.85 V +/-1.5% from +3.3V_VTX; EN = PA_EN (GPIO21), internal pull-down. VIN >= 3.15 V; PA internal 2k load meets IOUT >= 1 mA. C122/C123 4.7 uF local bypass.
U21 LP5912-3.3 on +5V, CIN = C13 on POWER if within 1 cm. EN = RP2354 GPIO19 (HD_EN). High = analog enabled; low = HD / analog off. R68 10k holds analog on during reset. C108 at VCO supply.
PA_DET: DET -> R66 1k / C117 100p -> ESP32 GPIO36, RC at the ESP32 end. J1 U.FL with the L2 plane cut out under the signal pad, >= 4 GND vias.
SE5004L (EK1 layout): RFout -> FL2 directly, no match parts. VCC on +BATT; decoupling at pins 8/9, 18/19, 20 + C118 10 uF. EP and GND pins to a via field.
VIDEO_OUT -> R58 || C104, R59, C105, R60 -> VT_MOD with R61/R62 bias; loop filter CP -> R63 -> VT, C106, R64 + C107. High-impedance (Analog class): short copper, >= 5 mm from boost and ESC phases.
ESP32 GPIO33 VTX_AMP_PWM -> 2 RC poles -> Q27 BC857 with emitter R73 -> PAOUT1 supply: sets the RTC6705 output-stage current. R73 10R; at the top step R73/R65/Q27 run near derated ratings.
RTC6705 pin 40 fed via R89 51R + C135 1u; pin 17 via R90 3.3k + C136 1u to GND. X4 8 MHz exactly, CL 10 pF.
PAOUT1 feed: L3 4.7 nH choke from PAOUT1_SUP (C109), C110 10 pF DC block into the PA input. Only these between pin 35 and the PA: 50 Ohm CPWG < 5 mm, RF class.
R80/R81/R82 1k in series on the SPI lines, placed at the ESP32 end: they limit back-feed into the unpowered RTC6705 in HD mode.

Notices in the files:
parts and their libraries:
3D: KiCad stock QFN-48-1EP_7x7mm_P0.5mm_EP5.6x5.6mm (CC-BY-SA 4.0), z scaled to 0.94 mm.
